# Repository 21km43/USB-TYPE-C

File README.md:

# USB-TYPE-C
USB Type-C Device board

This project is made with [KiCAD](https://kicad.org).

# Features

* 350mA Resettable Fuse
* Configuration Channel(CC) -> Pull downed with 5.1kΩ Resistor
* 10μF Capacitor

# Board Image

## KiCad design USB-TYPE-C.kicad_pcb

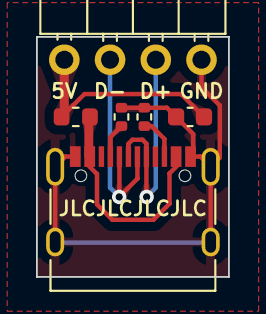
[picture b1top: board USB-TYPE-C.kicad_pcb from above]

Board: 2 copper layers, 10.7 x 13.3 mm, 6 parts (0 on the bottom side), 7 nets.

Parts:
C1: 10μF; C_0603_1608Metric
F1: MF-FSMF035X-2; Fuse_0603_1608Metric
J1: USB_C_Receptacle_USB2.0_16P; USB_C_Receptacle_XKB_U262-16XN-4BVC11
J2: Conn_01x04; PinHeader_1x04_P2.54mm_Horizontal
R1, R2: 5.1kΩ; R_0402_1005Metric

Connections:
D+: J1.A6 (D+), J1.B6 (D+), J2.3
D-: J1.A7 (D-), J1.B7 (D-), J2.2
GND: C1.2, J1.A1 (GND), J1.A12 (GND), J1.B1 (GND), J1.B12 (GND), J1.S1 (SHIELD), J2.4, R1.1, R2.1
unnamed: J1.A5 (CC1), R1.2
unnamed: J1.B5 (CC2), R2.2
VBUS: F1.1, J1.A4 (VBUS), J1.A9 (VBUS), J1.B4 (VBUS), J1.B9 (VBUS)
VCC: C1.1, F1.2, J2.1

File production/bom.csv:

Designator,Footprint,Quantity,Value,LCSC Part #
C1,0603,1,10μF,C96446
F1,0603,1,MF-FSMF035X-2,
J1,USB_C_Receptacle_XKB_U262-16XN-4BVC11,1,USB_C_Receptacle_USB2.0,C2765186
"R1, R2",0402,2,5.1kΩ,C25905

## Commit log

2024-03-16 Create LICENSE
